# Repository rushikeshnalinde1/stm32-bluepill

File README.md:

# stm32-bluepill
my attempt at creating the stm32 bluepill

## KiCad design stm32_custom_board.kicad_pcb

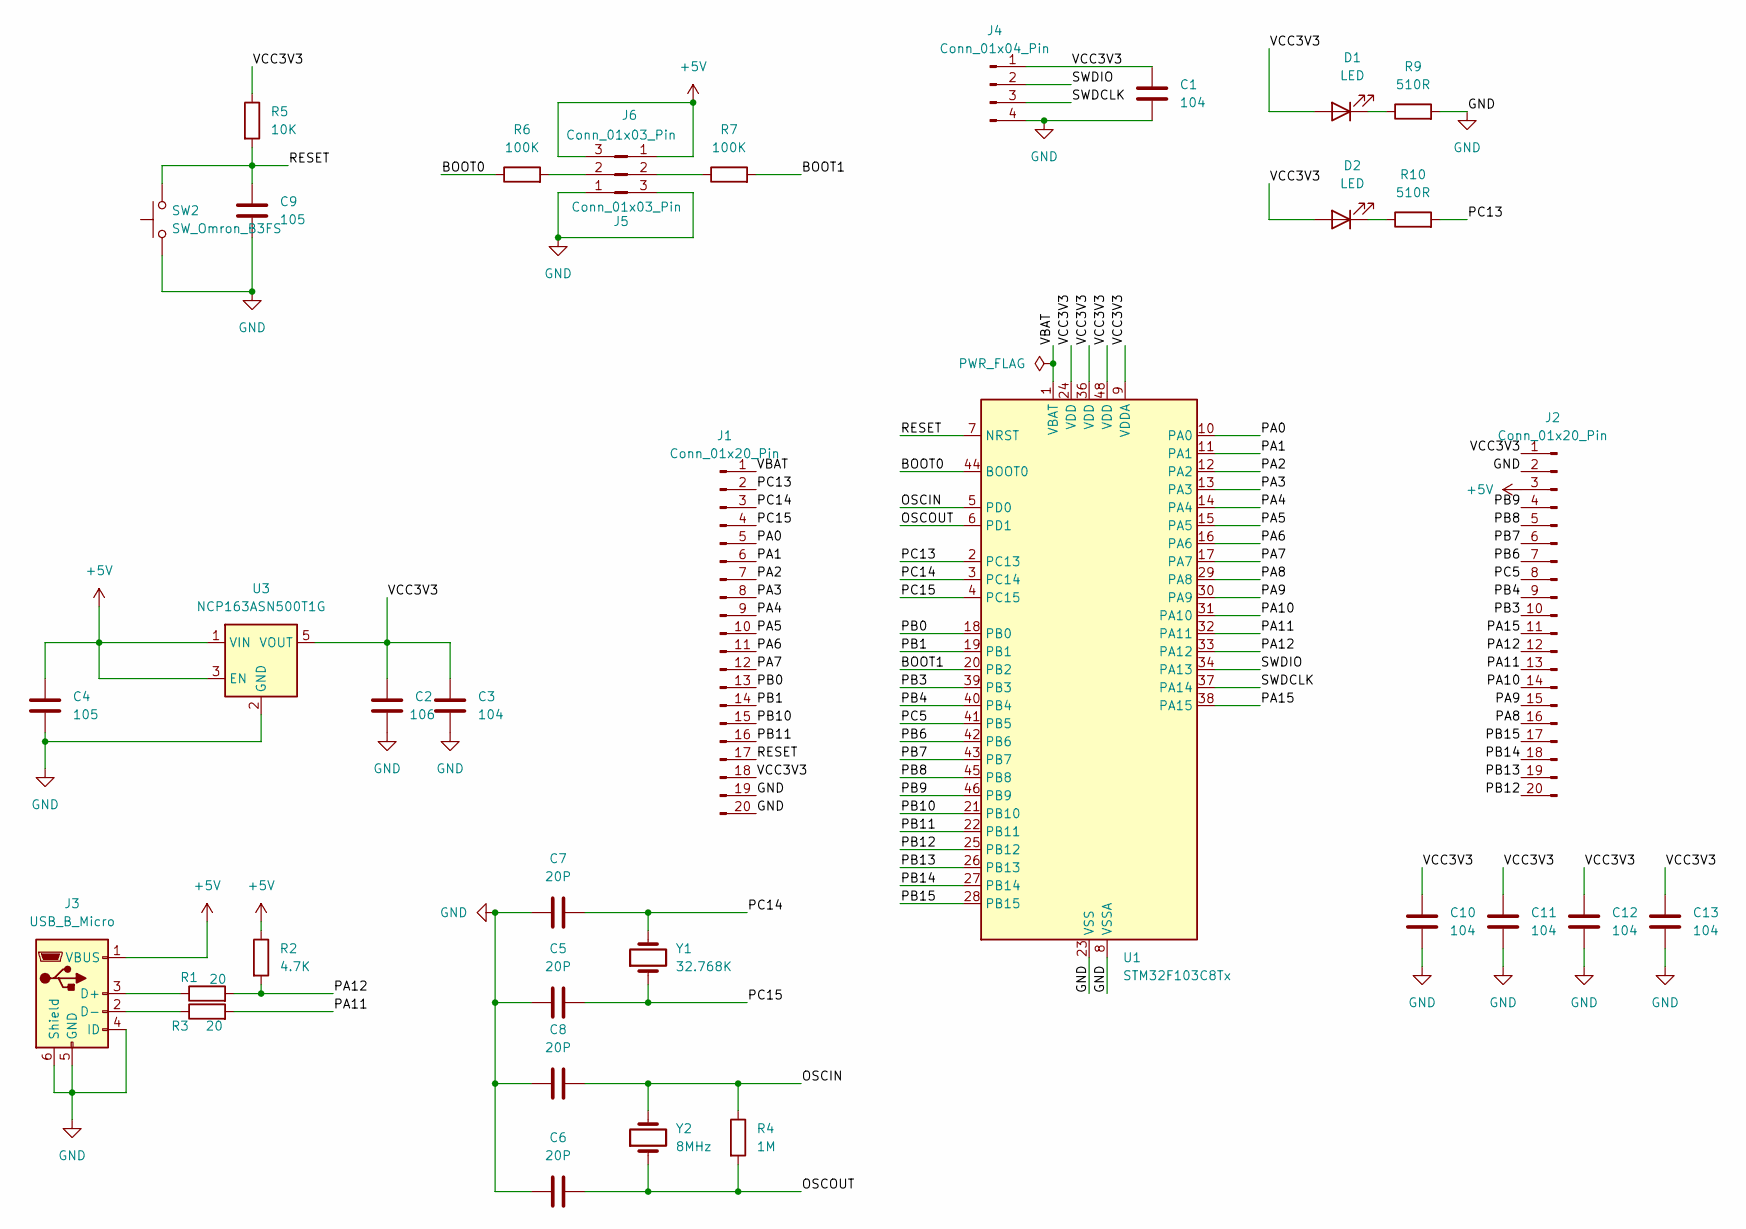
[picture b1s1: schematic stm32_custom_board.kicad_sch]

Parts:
C1, C3, C10, C11, C12, C13: 104; C_0201_0603Metric
C2: 106; C_0201_0603Metric
C4, C9: 105; C_0201_0603Metric
C5, C6, C7, C8: 20P; C_0201_0603Metric
D1, D2: LED; LED_0201_0603Metric
J1, J2: Conn_01x20_Pin; PinHeader_1x20_P2.54mm_Vertical
J3: USB_B_Micro; USB_Micro-AB_Molex_47590-0001
J4: Conn_01x04_Pin; PinHeader_1x04_P2.00mm_Horizontal
J5, J6: Conn_01x03_Pin; PinHeader_1x03_P1.00mm_Vertical
R1, R3: 20; R_0201_0603Metric
R2: 4.7K; R_0201_0603Metric
R4: 1M; R_0201_0603Metric
R5: 10K; R_0201_0603Metric
R6, R7: 100K; R_0201_0603Metric
R9, R10: 510R; R_0201_0603Metric
SW2: SW_Omron_B3FS; SW_SPST_Omron_B3FS-100xP
U1: STM32F103C8Tx; LQFP-48_7x7mm_P0.5mm
U3: NCP163ASN500T1G; SOT-23-5
Y1: 32.768K; Crystal_SMD_TXC_AX_8045-2Pin_8.0x4.5mm
Y2: 8MHz; Crystal_HC49-4H_Vertical

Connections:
+5V: C4.1, J2.3, J3.1 (VBUS), J5.1, J6.3, R2.1, U3.1 (VIN), U3.3 (EN)
/BOOT0: R6.1, U1.44 (BOOT0)
/BOOT1: R7.2, U1.20 (PB2)
/OSCIN: C8.1, R4.1, U1.5 (PD0), Y2.2
/OSCOUT: C6.2, R4.2, U1.6 (PD1), Y2.1
/PA0: J1.5, U1.10 (PA0)
/PA1: J1.6, U1.11 (PA1)
/PA2: J1.7, U1.12 (PA2)
/PA3: J1.8, U1.13 (PA3)
/PA4: J1.9, U1.14 (PA4)
/PA5: J1.10, U1.15 (PA5)
/PA6: J1.11, U1.16 (PA6)
/PA7: J1.12, U1.17 (PA7)
/PA8: J2.16, U1.29 (PA8)
/PA9: J2.15, U1.30 (PA9)
/PA10: J2.14, U1.31 (PA10)
/PA11: J2.13, R3.2, U1.32 (PA11)
/PA12: J2.12, R1.2, R2.2, U1.33 (PA12)
/PA15: J2.11, U1.38 (PA15)
/PB0: J1.13, U1.18 (PB0)
/PB1: J1.14, U1.19 (PB1)
/PB3: J2.10, U1.39 (PB3)
/PB4: J2.9, U1.40 (PB4)
/PB6: J2.7, U1.42 (PB6)
/PB7: J2.6, U1.43 (PB7)
/PB8: J2.5, U1.45 (PB8)
/PB9: J2.4, U1.46 (PB9)
/PB10: J1.15, U1.21 (PB10)
/PB11: J1.16, U1.22 (PB11)
/PB12: J2.20, U1.25 (PB12)
/PB13: J2.19, U1.26 (PB13)
/PB14: J2.18, U1.27 (PB14)
/PB15: J2.17, U1.28 (PB15)
/PC5: J2.8, U1.41 (PB5)
/PC13: J1.2, R10.2, U1.2 (PC13)
/PC14: C7.1, J1.3, U1.3 (PC14), Y1.2
/PC15: C5.2, J1.4, U1.4 (PC15), Y1.1
/RESET: C9.1, J1.17, R5.2, SW2.2, U1.7 (NRST)
/SWDCLK: J4.3, U1.37 (PA14)
/SWDIO: J4.2, U1.34 (PA13)
/VBAT: J1.1, U1.1 (VBAT)
/VCC3V3: C1.1, C2.1, C3.1, C10.1, C11.1, C12.1, C13.1, D1.2 (A), D2.2 (A), J1.18, J2.1, J4.1, R5.1, U1.9 (VDDA), U1.24 (VDD), U1.36 (VDD), U1.48 (VDD), U3.5 (VOUT)
GND: C1.2, C2.2, C3.2, C4.2, C5.1, C6.1, C7.2, C8.2, C9.2, C10.2, C11.2, C12.2, C13.2, J1.19, J1.20, J2.2, J3.4 (ID), J3.5 (GND), J3.6 (Shield), J4.4, J5.3, J6.1, R9.2, SW2.1, U1.8 (VSSA), U1.23 (VSS), U1.35 (VSS), U1.47 (VSS), U3.2 (GND)
unnamed: D1.1 (K), R9.1
unnamed: D2.1 (K), R10.1
unnamed: J3.3 (D+), R1.1
unnamed: J3.2 (D-), R3.1
unnamed: J5.2, R7.1
unnamed: J6.2, R6.2

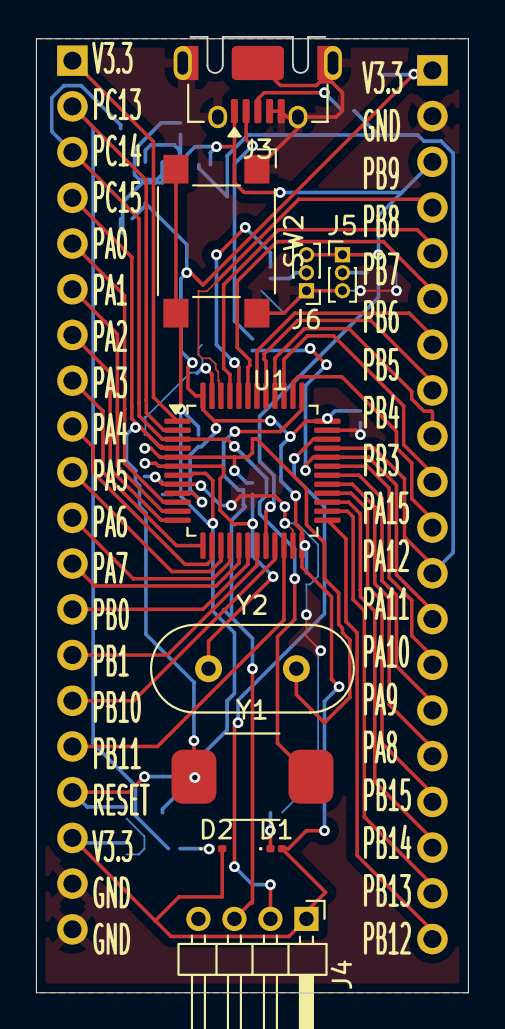
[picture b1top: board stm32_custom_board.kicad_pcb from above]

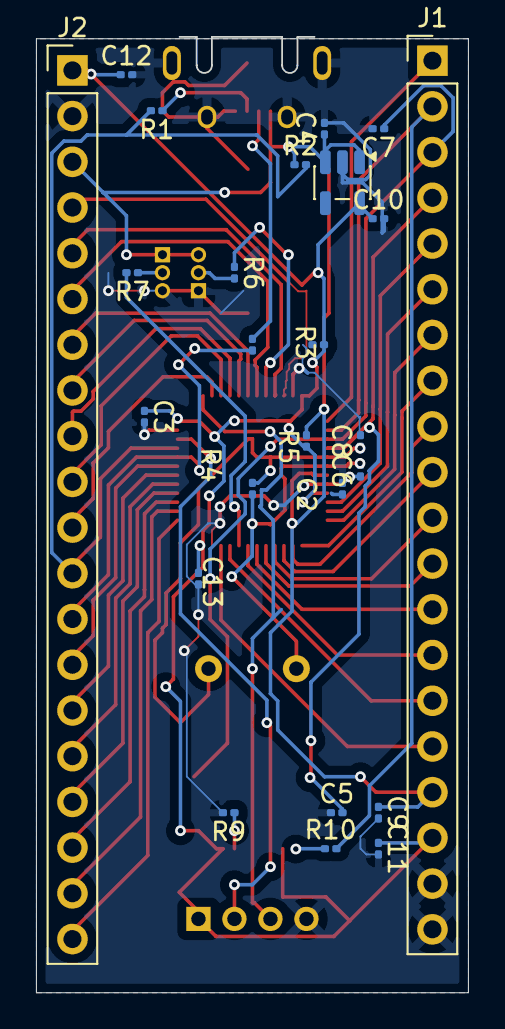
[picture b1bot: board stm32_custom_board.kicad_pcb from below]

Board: 2 copper layers, 24.0 x 53.1 mm, 35 parts (25 on the bottom side), 49 nets.
